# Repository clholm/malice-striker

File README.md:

# malice-striker
RAT and DRV-inspired overdrive with a Baxandall EQ

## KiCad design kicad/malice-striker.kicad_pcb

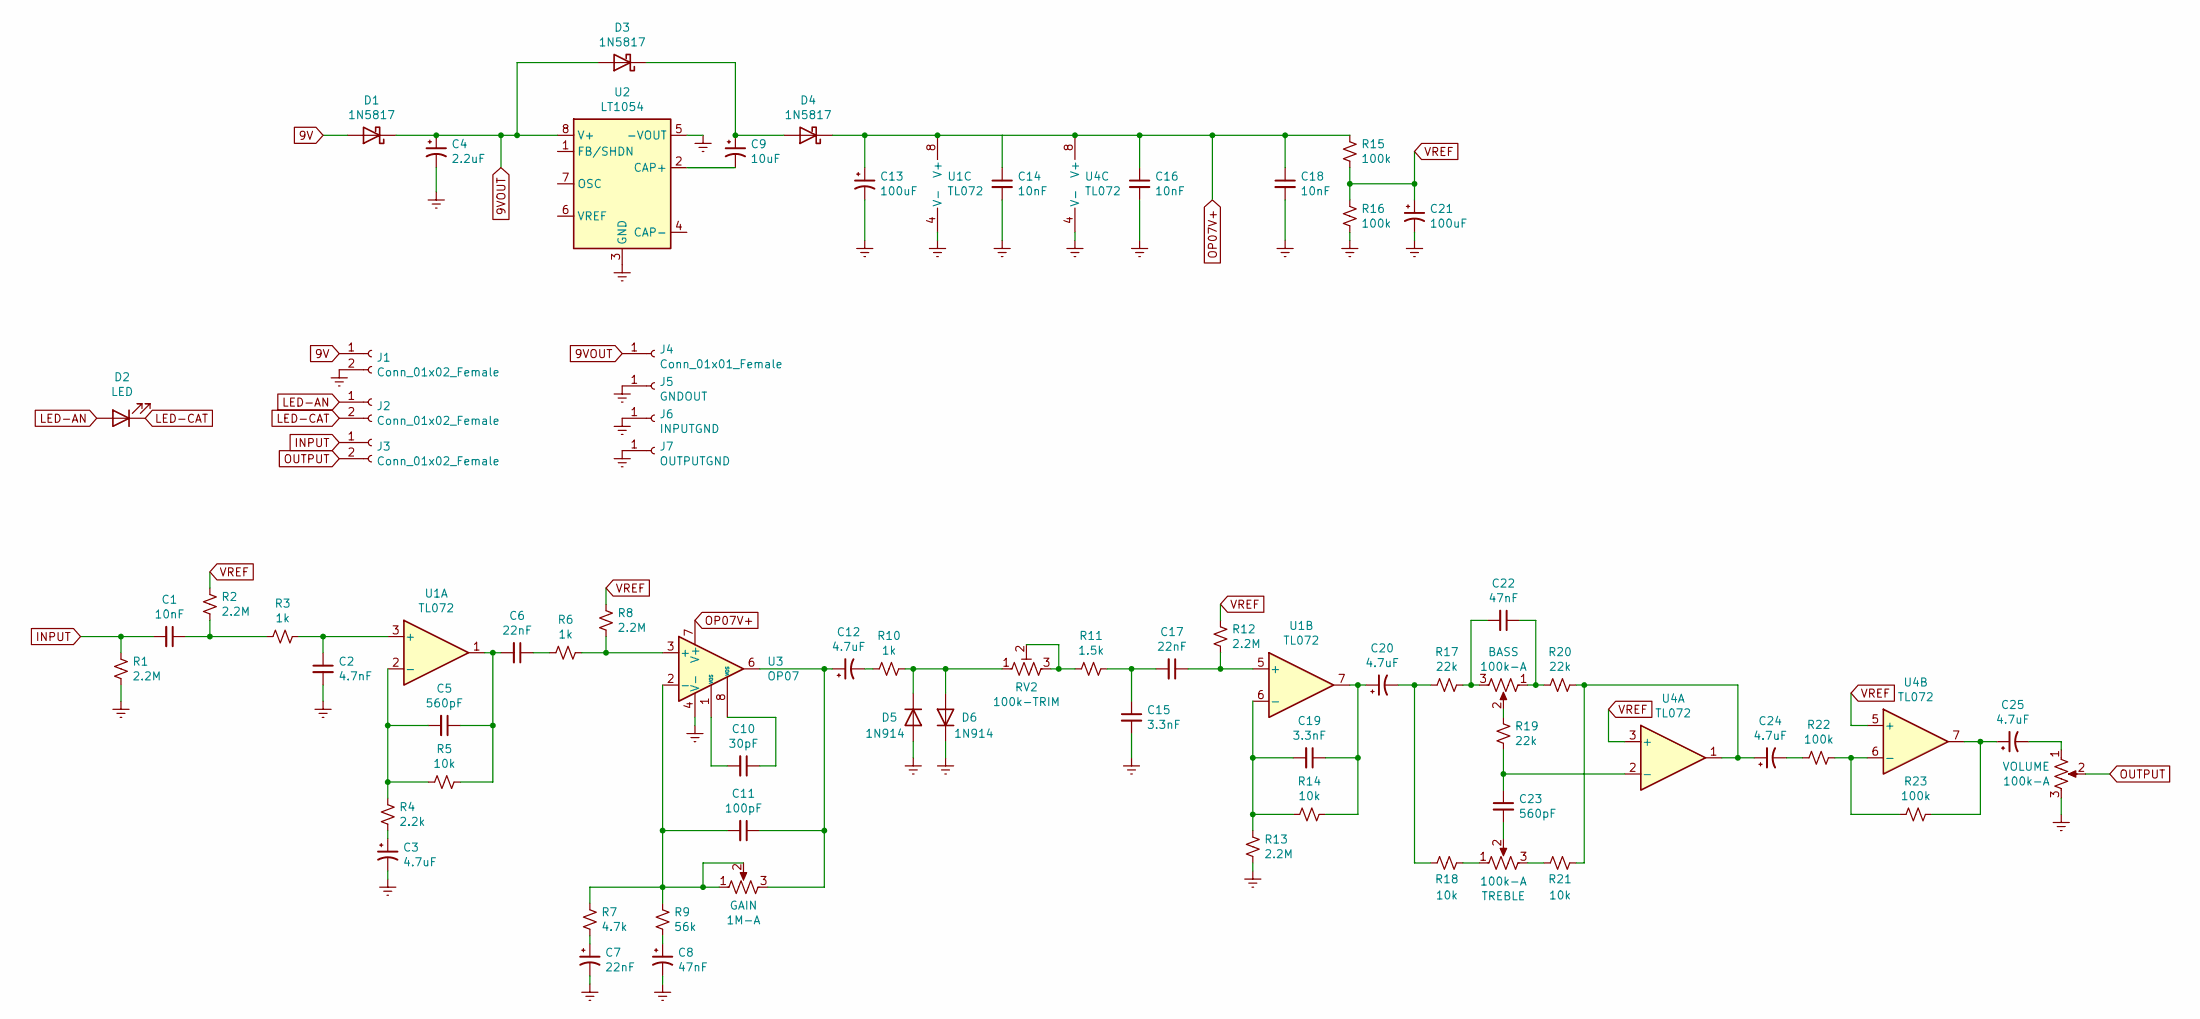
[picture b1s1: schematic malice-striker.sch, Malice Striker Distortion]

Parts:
BASS: 100k-A; 16MM_T.MOUNT
C1, C14, C16, C18: 10nF; C_Rect_L7.2mm_W2.5mm_P5.00mm_FKS2_FKP2_MKS2_MKP2
C2: 4.7nF; C_Rect_L7.2mm_W2.5mm_P5.00mm_FKS2_FKP2_MKS2_MKP2
C3, C12, C20, C24, C25: 4.7uF; CP_Radial_D5.0mm_P2.00mm
C4: 2.2uF; CP_Radial_D5.0mm_P2.00mm
C5, C23: 560pF; C_Rect_L7.2mm_W5.5mm_P5.00mm_FKS2_FKP2_MKS2_MKP2
C6, C7: 22nF; C_Rect_L7.2mm_W2.5mm_P5.00mm_FKS2_FKP2_MKS2_MKP2
C8, C22: 47nF; C_Rect_L7.2mm_W2.5mm_P5.00mm_FKS2_FKP2_MKS2_MKP2
C9: 10uF; CP_Radial_D5.0mm_P2.00mm
C10: 30pF; C_Rect_L4.0mm_W2.5mm_P2.50mm
C11: 100pF; C_Rect_L4.6mm_W4.6mm_P2.50mm_MKS02_FKP02
C13, C21: 100uF; CP_Radial_D6.3mm_P2.50mm
C15, C19: 3.3nF; C_Rect_L7.0mm_W4.5mm_P5.00mm
C17: 22nF; C_Rect_L7.2mm_W5.5mm_P5.00mm_FKS2_FKP2_MKS2_MKP2
D1, D3, D4: 1N5817; D_DO-41_SOD81_P10.16mm_Horizontal
D2: LED; LED_D5.0mm
D5, D6: 1N914; D_DO-35_SOD27_P7.62mm_Horizontal
GAIN: 1M-A; 16MM_T.MOUNT
J1, J2, J3: Conn_01x02_Female; PinSocket_1x02_P2.54mm_Vertical
J4: Conn_01x01_Female; PinSocket_1x01_P2.54mm_Vertical
J5: GNDOUT; PinSocket_1x01_P2.54mm_Vertical
J6: INPUTGND; PinSocket_1x01_P2.54mm_Vertical
J7: OUTPUTGND; PinSocket_1x01_P2.54mm_Vertical
R1, R2, R8, R12, R13: 2.2M; R_Axial_DIN0207_L6.3mm_D2.5mm_P7.62mm_Horizontal
R3, R6, R10: 1k; 0.3_resistor
R4: 2.2k; R_Axial_DIN0207_L6.3mm_D2.5mm_P7.62mm_Horizontal
R5, R14, R18, R21: 10k; 0.3_resistor
R7: 4.7k; 0.3_resistor
R9: 56k; R_Axial_DIN0207_L6.3mm_D2.5mm_P7.62mm_Horizontal
R11: 1.5k; R_Axial_DIN0207_L6.3mm_D2.5mm_P7.62mm_Horizontal
R15, R16, R22, R23: 100k; R_Axial_DIN0207_L6.3mm_D2.5mm_P7.62mm_Horizontal
R17, R19, R20: 22k; R_Axial_DIN0207_L6.3mm_D2.5mm_P7.62mm_Horizontal
RV2: 100k-TRIM; Potentiometer_Vishay_T73YP_Vertical
TREBLE: 100k-A; 16MM_T.MOUNT
U1, U4: TL072; SOT-23-8_Handsoldering
U2: LT1054; DIP-8_W10.16mm
U3: OP07; SOIC-8-1EP_3.9x4.9mm_P1.27mm_EP2.29x3mm
VOLUME: 100k-A; 16MM_T.MOUNT

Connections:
9V: D1.2 (A), J1.1
9VOUT: C4.1, D1.1 (K), D3.2 (A), J4.1, U2.8 (V+); also elsewhere on the board
Earth: C2.2, C3.2, C4.2, C7.2, C8.2, C13.2, C14.2, C15.2, C16.2, C18.2, C21.2, D5.2 (A), D6.1 (K), J1.2, J5.1, J6.1, J7.1, R1.2, R13.2, R16.2, U1.4 (V-), U2.3 (GND), U2.5 (-VOUT), U3.4 (V-), U4.4 (V-), VOLUME.3
INPUT: C1.2, J3.1, R1.1
LED-AN: D2.2 (A), J2.1
LED-CAT: D2.1 (K), J2.2
unnamed: BASS.1, C22.1, R20.2
unnamed: BASS.2, R19.1
unnamed: BASS.3, C22.2, R17.1
unnamed: C1.1, R2.2, R3.2
unnamed: C2.1, R3.1, U1.3 (+)
unnamed: C3.1, R4.2
unnamed: C5.1, C6.2, R5.1, U1.1
unnamed: C5.2, R4.1, R5.2, U1.2 (-)
unnamed: C6.1, R6.2
unnamed: C7.1, R7.2
unnamed: C8.1, R9.2
unnamed: C9.1, D3.1 (K), D4.2 (A)
unnamed: C9.2, U2.2 (CAP+)
unnamed: C10.1, U3.8 (VOS)
unnamed: C10.2, U3.1 (VOS)
unnamed: C11.1, C12.1, GAIN.3, U3.6
unnamed: C11.2, GAIN.1, GAIN.2, R7.1, R9.1, U3.2 (-)
unnamed: C12.2, R10.2
unnamed: C15.1, C17.2, R11.1
unnamed: C17.1, R12.2, U1.5 (+)
unnamed: C19.1, C20.1, R14.1, U1.7
unnamed: C19.2, R13.1, R14.2, U1.6 (-)
unnamed: C20.2, R17.2, R18.1
unnamed: C23.1, R19.2, U4.2 (-)
unnamed: C23.2, TREBLE.2
unnamed: C24.1, R20.1, R21.2, U4.1
unnamed: C24.2, R22.2
unnamed: C25.1, R23.1, U4.7
unnamed: C25.2, VOLUME.1
unnamed: D5.1 (K), D6.2 (A), R10.1, RV2.1
unnamed: R6.1, R8.2, U3.3 (+)
unnamed: R11.2, RV2.2, RV2.3
unnamed: R18.2, TREBLE.1
unnamed: R21.1, TREBLE.3
unnamed: R22.1, R23.2, U4.6 (-)
OP07V+: C13.1, C14.1, C16.1, C18.1, D4.1 (K), R15.1, U1.8 (V+), U3.7 (V+), U4.8 (V+)
OUTPUT: J3.2, VOLUME.2
VREF: C21.1, R2.1, R8.1, R12.1, R15.2, R16.1, U4.3 (+), U4.5 (+)

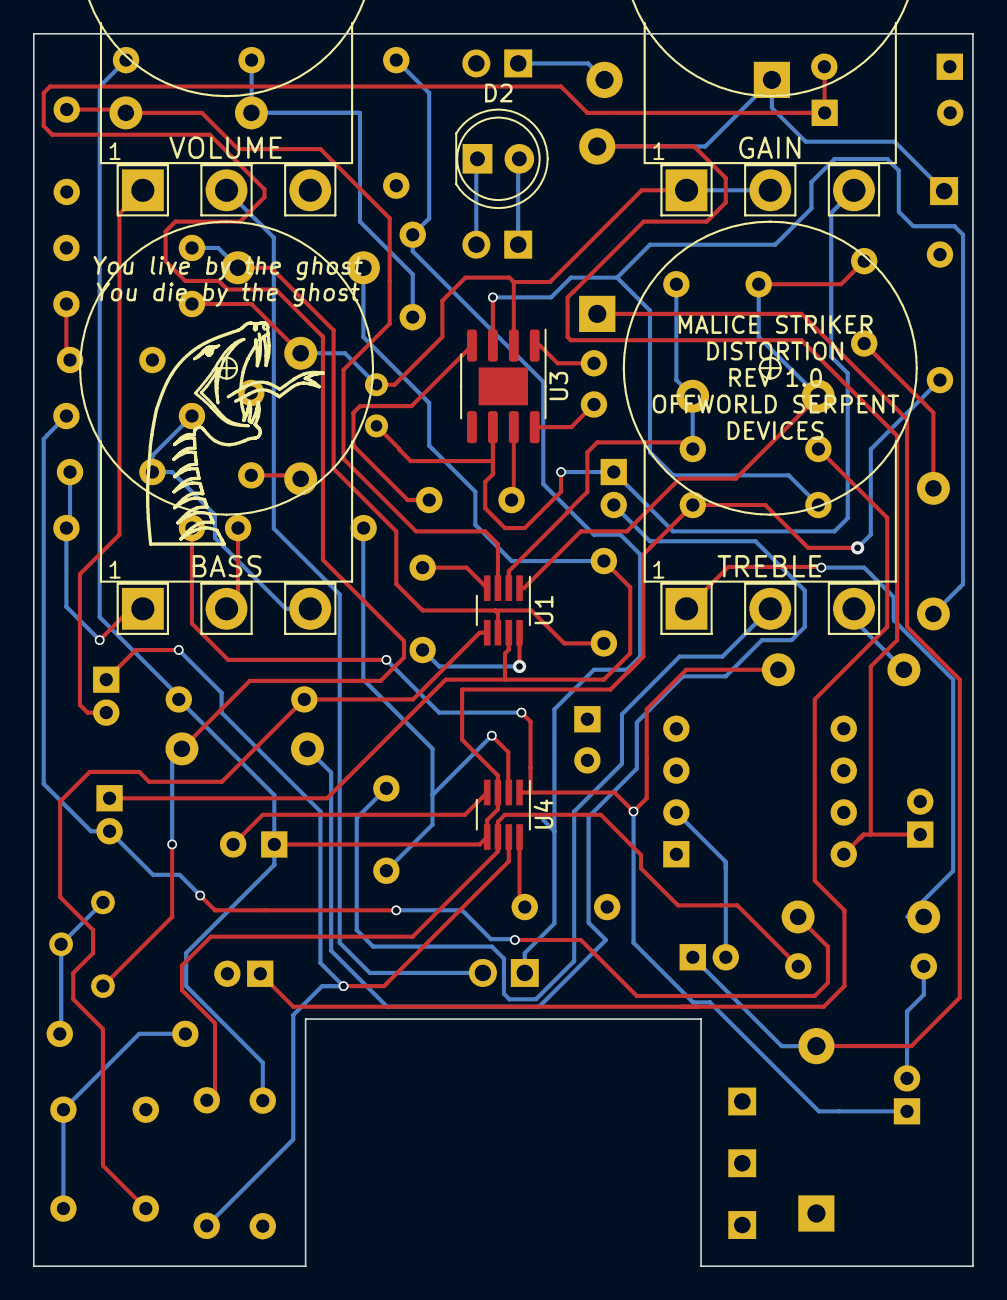
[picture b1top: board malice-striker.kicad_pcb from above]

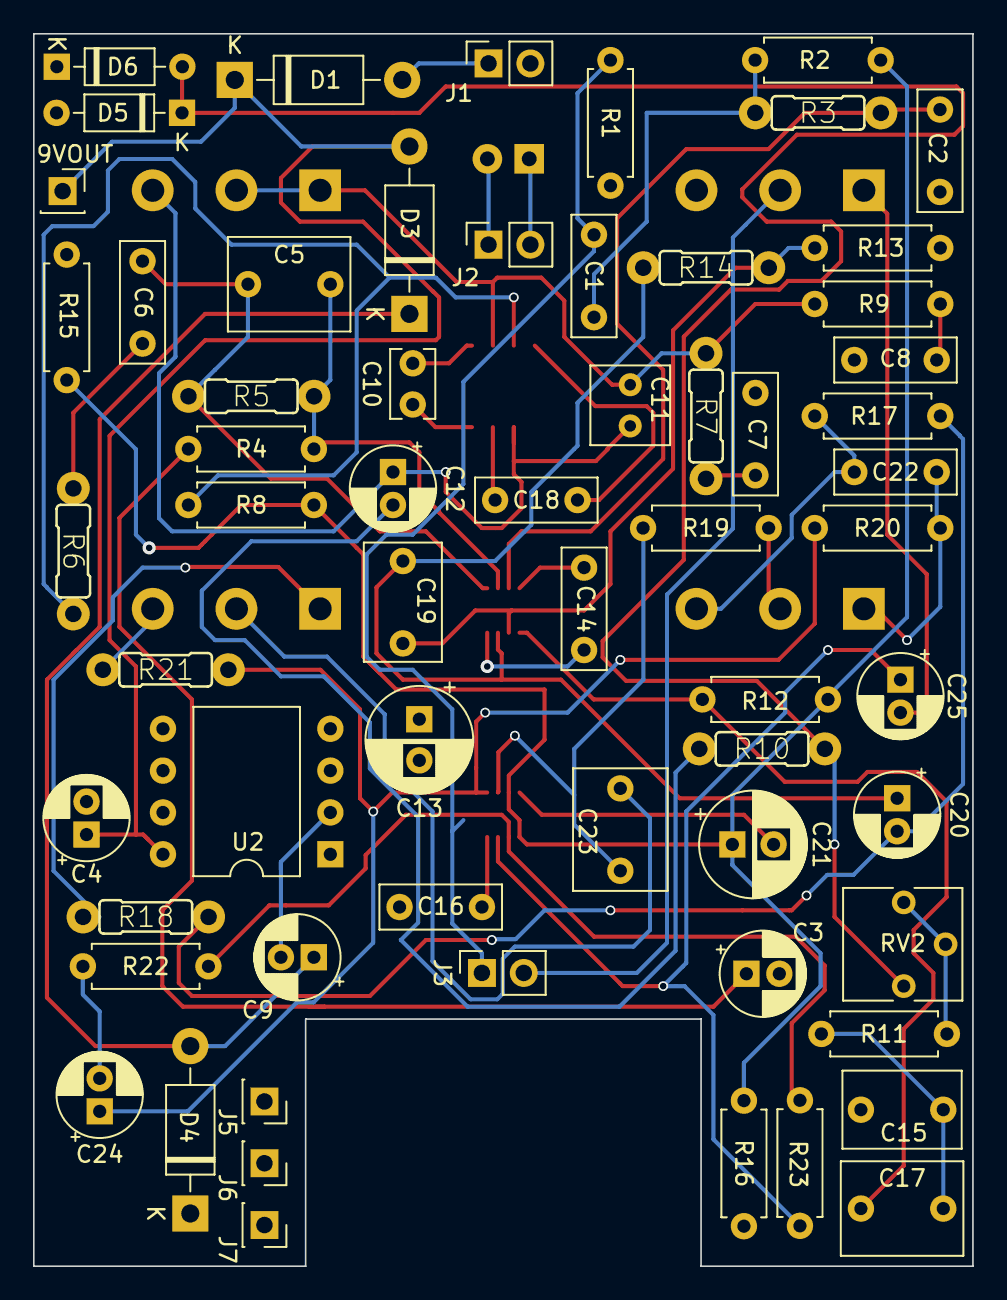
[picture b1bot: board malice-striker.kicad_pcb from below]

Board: 4 copper layers, 57.0 x 74.8 mm, 70 parts (62 on the bottom side), 44 nets.

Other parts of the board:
9VOUT: Conn_01x01_Female; PinSocket_1x01_P2.54mm_Vertical

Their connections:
9VOUT: 9VOUT.1; also elsewhere on the board

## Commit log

2021-01-01 initial commit with v1.0 schematic
2022-03-23 this board is a mess!
2022-03-26 modified pcb size a bit to fit stomp switch breakout
2022-03-26 deleted extra files
2022-03-26 added connections for LED and input/output grounds
2022-03-29 cleaned up PCB a bit
2022-04-21 v2 finished!
2022-04-22 v2 with rounded tracks
